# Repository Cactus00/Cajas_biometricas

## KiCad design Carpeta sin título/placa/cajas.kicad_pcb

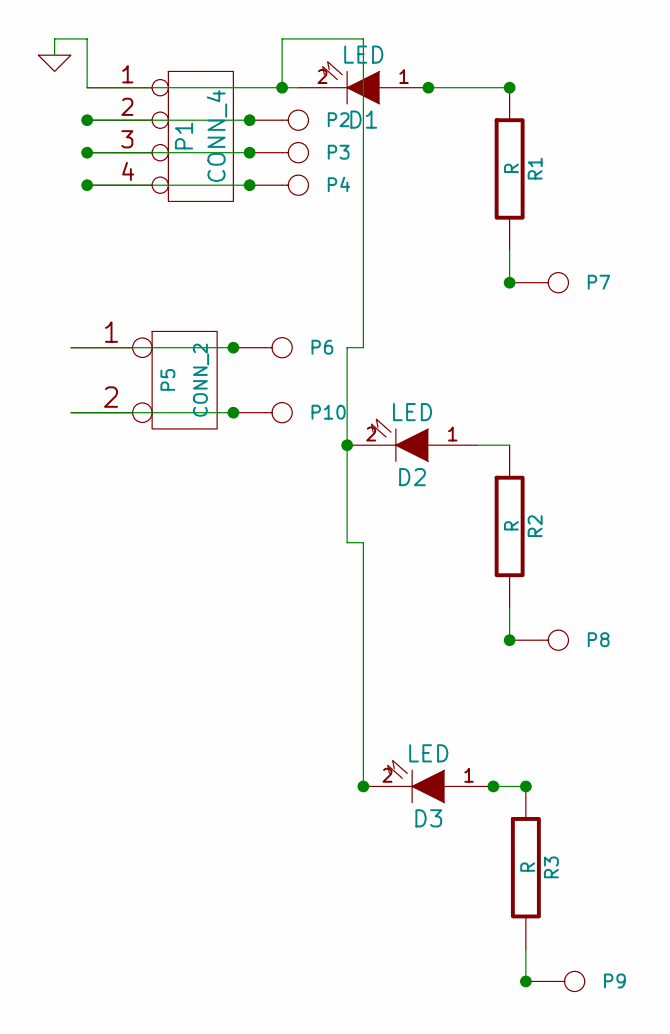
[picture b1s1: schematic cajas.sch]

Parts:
D1, D2, D3: LED
P1: CONN_4
P2, P3, P4, P6, P7, P8, P9, P10: CONN_1
P5: CONN_2
R1, R2, R3: R

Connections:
GND: D1.2 (K), D2.2 (K), D3.2 (K), P1.1
unnamed: P1.4, P4.1
unnamed: P1.3, P3.1
unnamed: P8.1, R2.2
unnamed: P7.1, R1.2
unnamed: P5.2 (PM), P10.1
unnamed: P5.1, P6.1
unnamed: P1.2, P2.1
unnamed: P9.1, R3.2
unnamed: D1.1 (A), R1.1
unnamed: D3.1 (A), R3.1
unnamed: D2.1 (A), R2.1

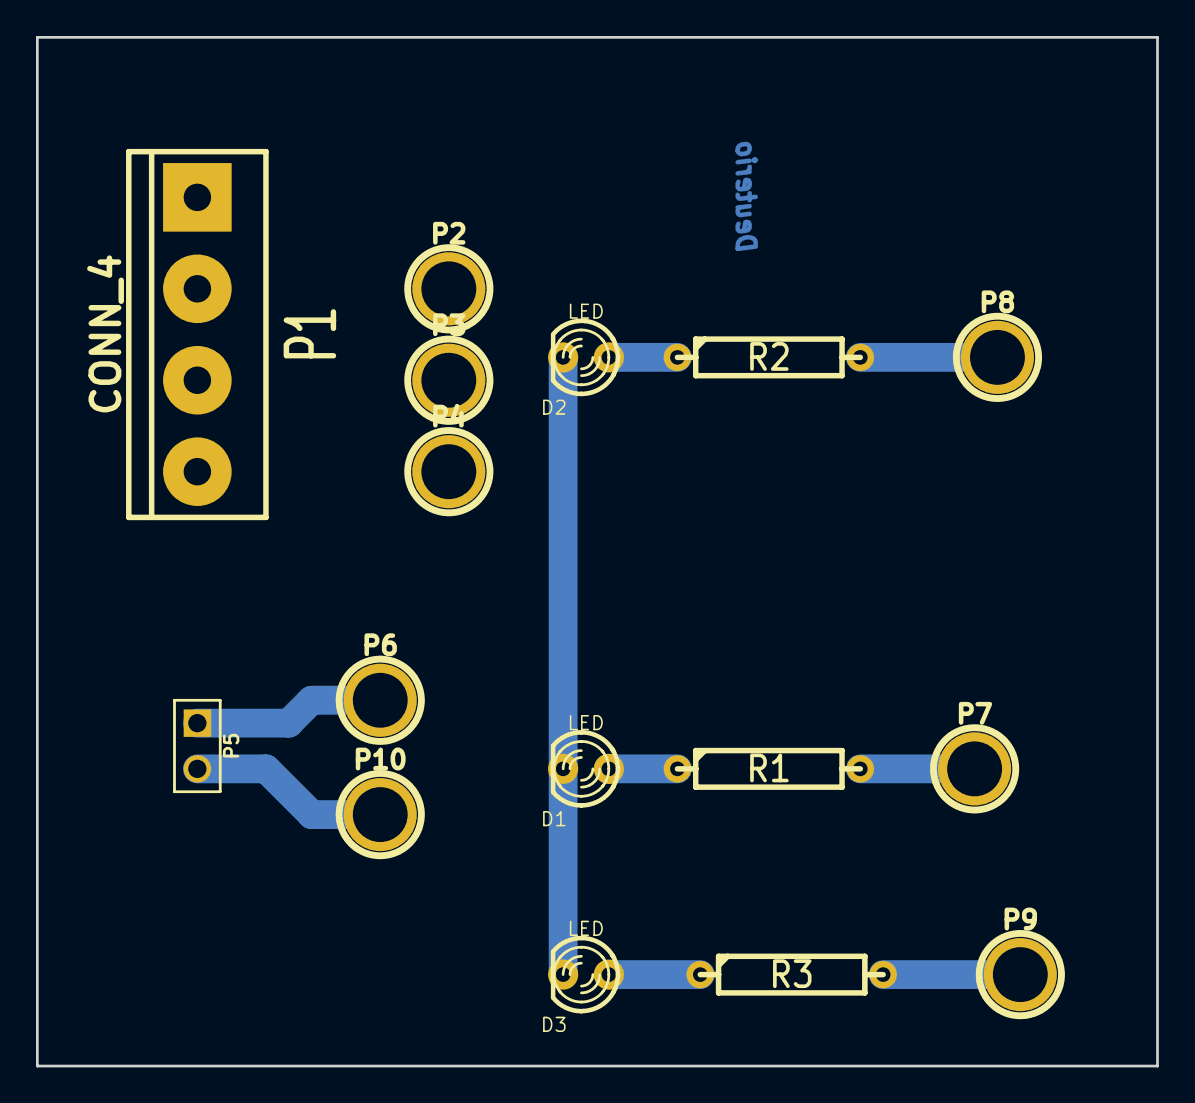
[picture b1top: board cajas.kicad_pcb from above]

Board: 2 copper layers, 62.2 x 57.2 mm, 16 parts (0 on the bottom side), 12 nets.

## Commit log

2016-12-27 Add files via upload
    Codigos_lectura_caja
2016-12-27 agregando
2016-12-27 cambio_nombre_carpeta_y_borrado_archivo
